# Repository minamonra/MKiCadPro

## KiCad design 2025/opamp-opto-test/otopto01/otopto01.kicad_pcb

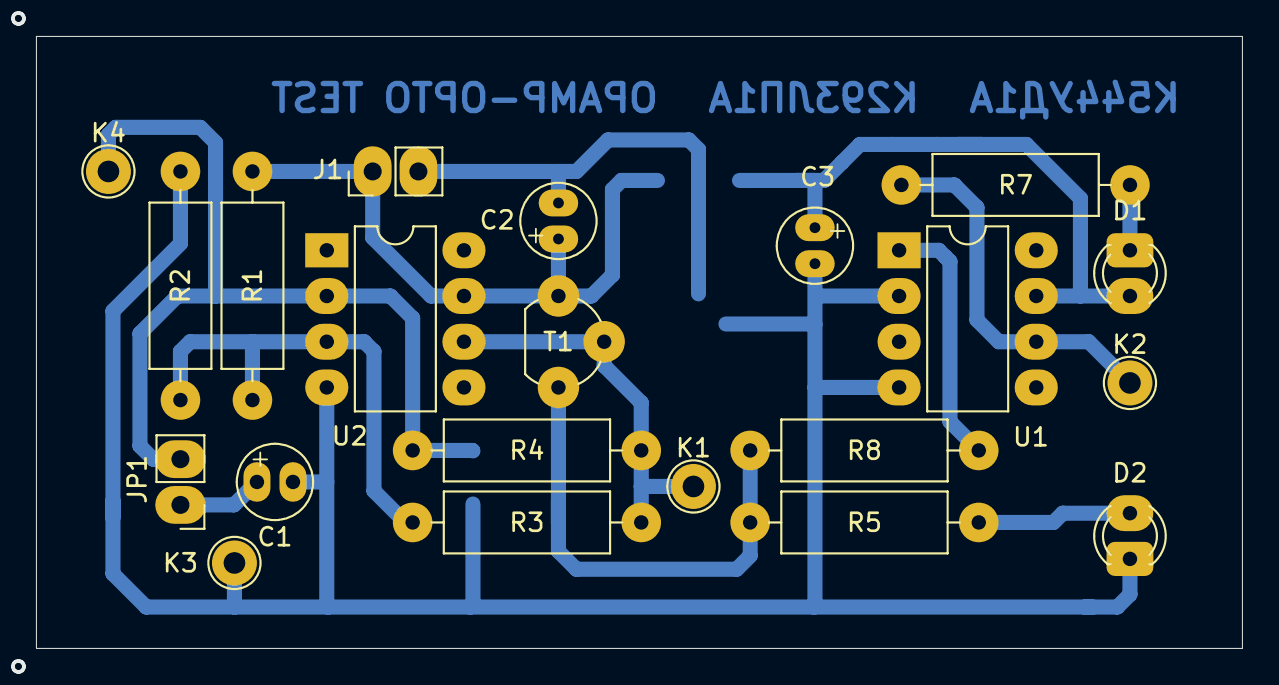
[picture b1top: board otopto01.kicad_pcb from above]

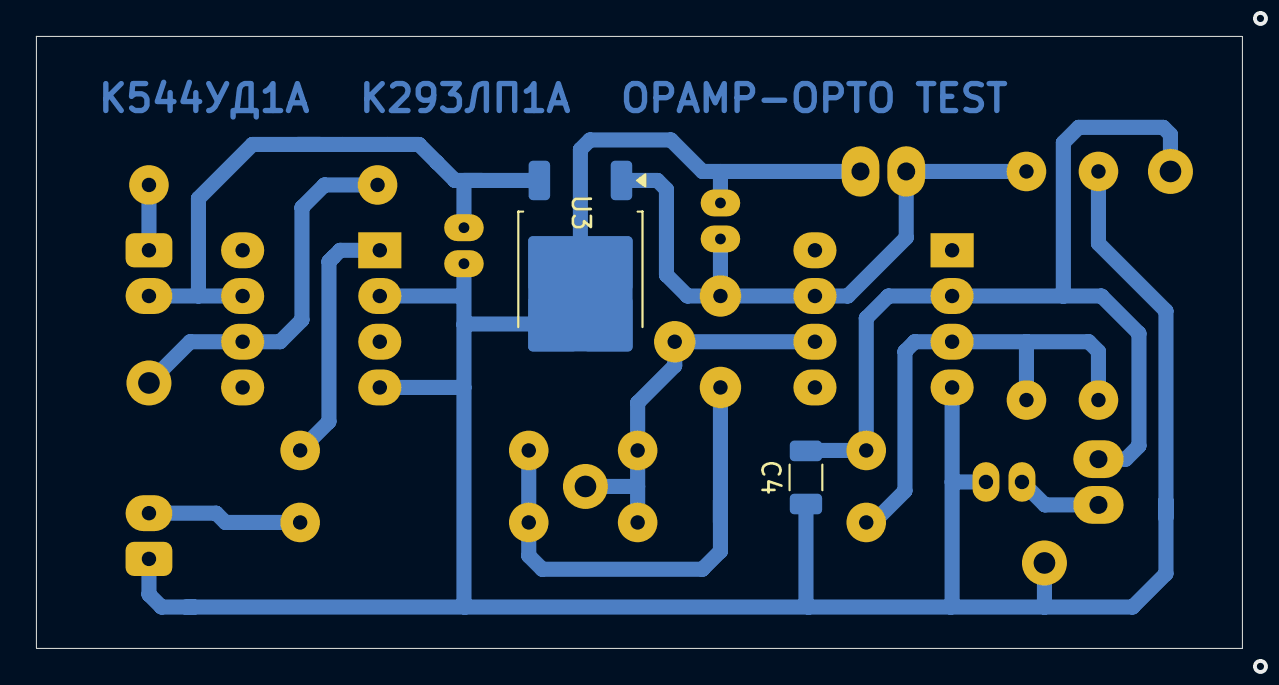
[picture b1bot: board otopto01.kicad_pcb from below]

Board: 2 copper layers, 67.0 x 34.0 mm, 23 parts (2 on the bottom side), 12 nets.

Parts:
C1, C2, C3: 47u; CPD4.0P2.00v1
C4: C_CAP; C_1206_3216Metric
D1, D2: LED; LED_D3.0mm
J1: Conn_2pin01; PinHeader_1x02_P2.54mm_Vertical
JP1: Jumper_2_Bridged; PinHeader_1x02_P2.54mm_Vertical
K1, K2, K3, K4: test_point; TestPoint_THTPad_D2.5mm_Drill1.2mm
R1, R2: 10k; R_Axial_DIN0309_L9.0mm_D3.2mm_P12.70mm_Horizontal
R3: 22k; R_Axial_DIN0309_L9.0mm_D3.2mm_P12.70mm_Horizontal
R4: 18k; R_Axial_DIN0309_L9.0mm_D3.2mm_P12.70mm_Horizontal
R5, R8: 330; R_Axial_DIN0309_L9.0mm_D3.2mm_P12.70mm_Horizontal
R7: 510; R_Axial_DIN0309_L9.0mm_D3.2mm_P12.70mm_Horizontal
T1: BC547; TO-92-01
U1: К293ЛП1А; DIP-8_W7.62mm_LongPads
U2: TL081; DIP-8_W7.62mm_LongPads
U3: LM78M05; TO-252-2

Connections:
/+5V: C3.1, D1.2 (A), U1.7, U3.3 (VO)
/+12V: C2.1, J1.1, R1.2, T1.1 (C), U2.7 (VCC), U3.1 (VI)
GND: C1.2, C2.2, C3.2, C4.1, D2.1 (C), J1.2, K3.1, R2.1, U1.2, U1.4, U2.4 (VDD), U3.2 (GND)
unnamed: D1.1 (C), R7.1
unnamed: D2.2 (A), R5.1
unnamed: C1.1, JP1.1 (A)
unnamed: C4.2, JP1.2 (B), K4.1, R4.1, U2.2 (IN-)
unnamed: K2.1, R7.2, U1.6
unnamed: R8.1, U1.1
unnamed: K1.1, R3.2, R4.2, T1.2 (B), U2.6 (OUT)
unnamed: R5.2, R8.2, T1.3 (E)
unnamed: R1.1, R2.2, R3.1, U2.3 (IN+)

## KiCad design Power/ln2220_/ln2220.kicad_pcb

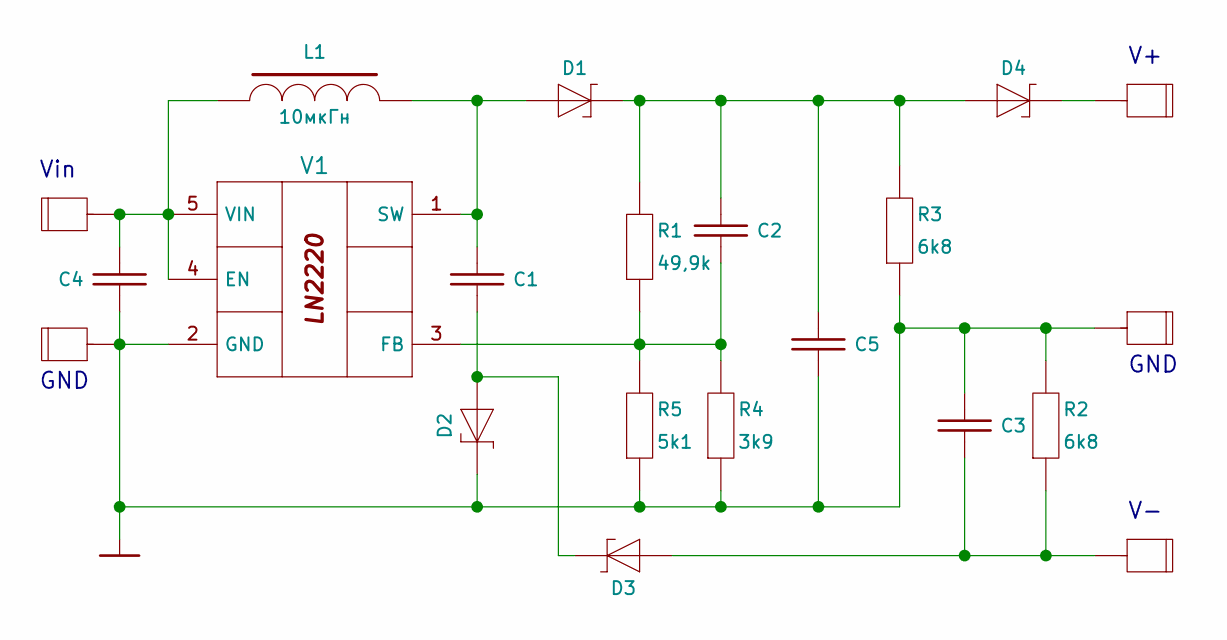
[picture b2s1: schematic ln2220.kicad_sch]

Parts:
C1, C3, C4, C5: C_0805_2012Metric
C2: C_0603_1608Metric
D1, D2, D3, D4: D_1206_3216Metric
J1, J2, J3, J4, J5: CONN01PIN; PinHeader_1x01_P2.54mm_Vertical
L1: 10мкГн; L_Coilcraft_LPS5030
R1: 49,9k; R_0603_1608Metric
R2, R3: 6k8; R_0805_2012Metric
R4: 3k9; R_0603_1608Metric
R5: 5k1; R_0603_1608Metric
V1: LN2220_; SOT-23-6

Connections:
GND: C3.2, C4.1, C5.1, D2.1 (C), J2.1, J4.1, R2.2, R3.1, R4.1, R5.1, V1.2 (GND)
unnamed: C1.2, D1.2 (A), L1.2, V1.1 (SW)
unnamed: C2.2, C5.2, D1.1 (C), D4.2 (A), R1.2, R3.2
unnamed: C1.1, D2.2 (A), D3.1 (C)
unnamed: C3.1, D3.2 (A), J5.1, R2.1
unnamed: D4.1 (C), J3.1
unnamed: C4.2, J1.1, L1.1, V1.4 (EN), V1.5 (VIN)
unnamed: C2.1, R1.1, R4.2, R5.2, V1.3 (FB)

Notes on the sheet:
Vin
GND

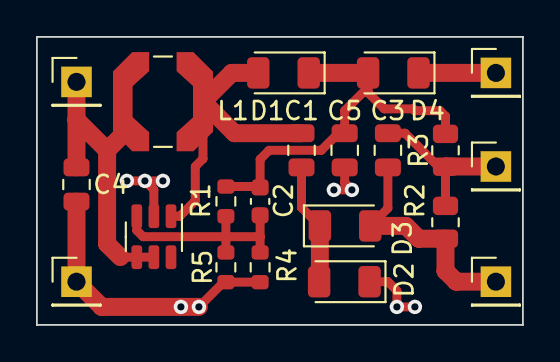
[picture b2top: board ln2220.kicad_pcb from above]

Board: 2 copper layers, 27.0 x 16.0 mm, 21 parts (0 on the bottom side), 8 nets.
